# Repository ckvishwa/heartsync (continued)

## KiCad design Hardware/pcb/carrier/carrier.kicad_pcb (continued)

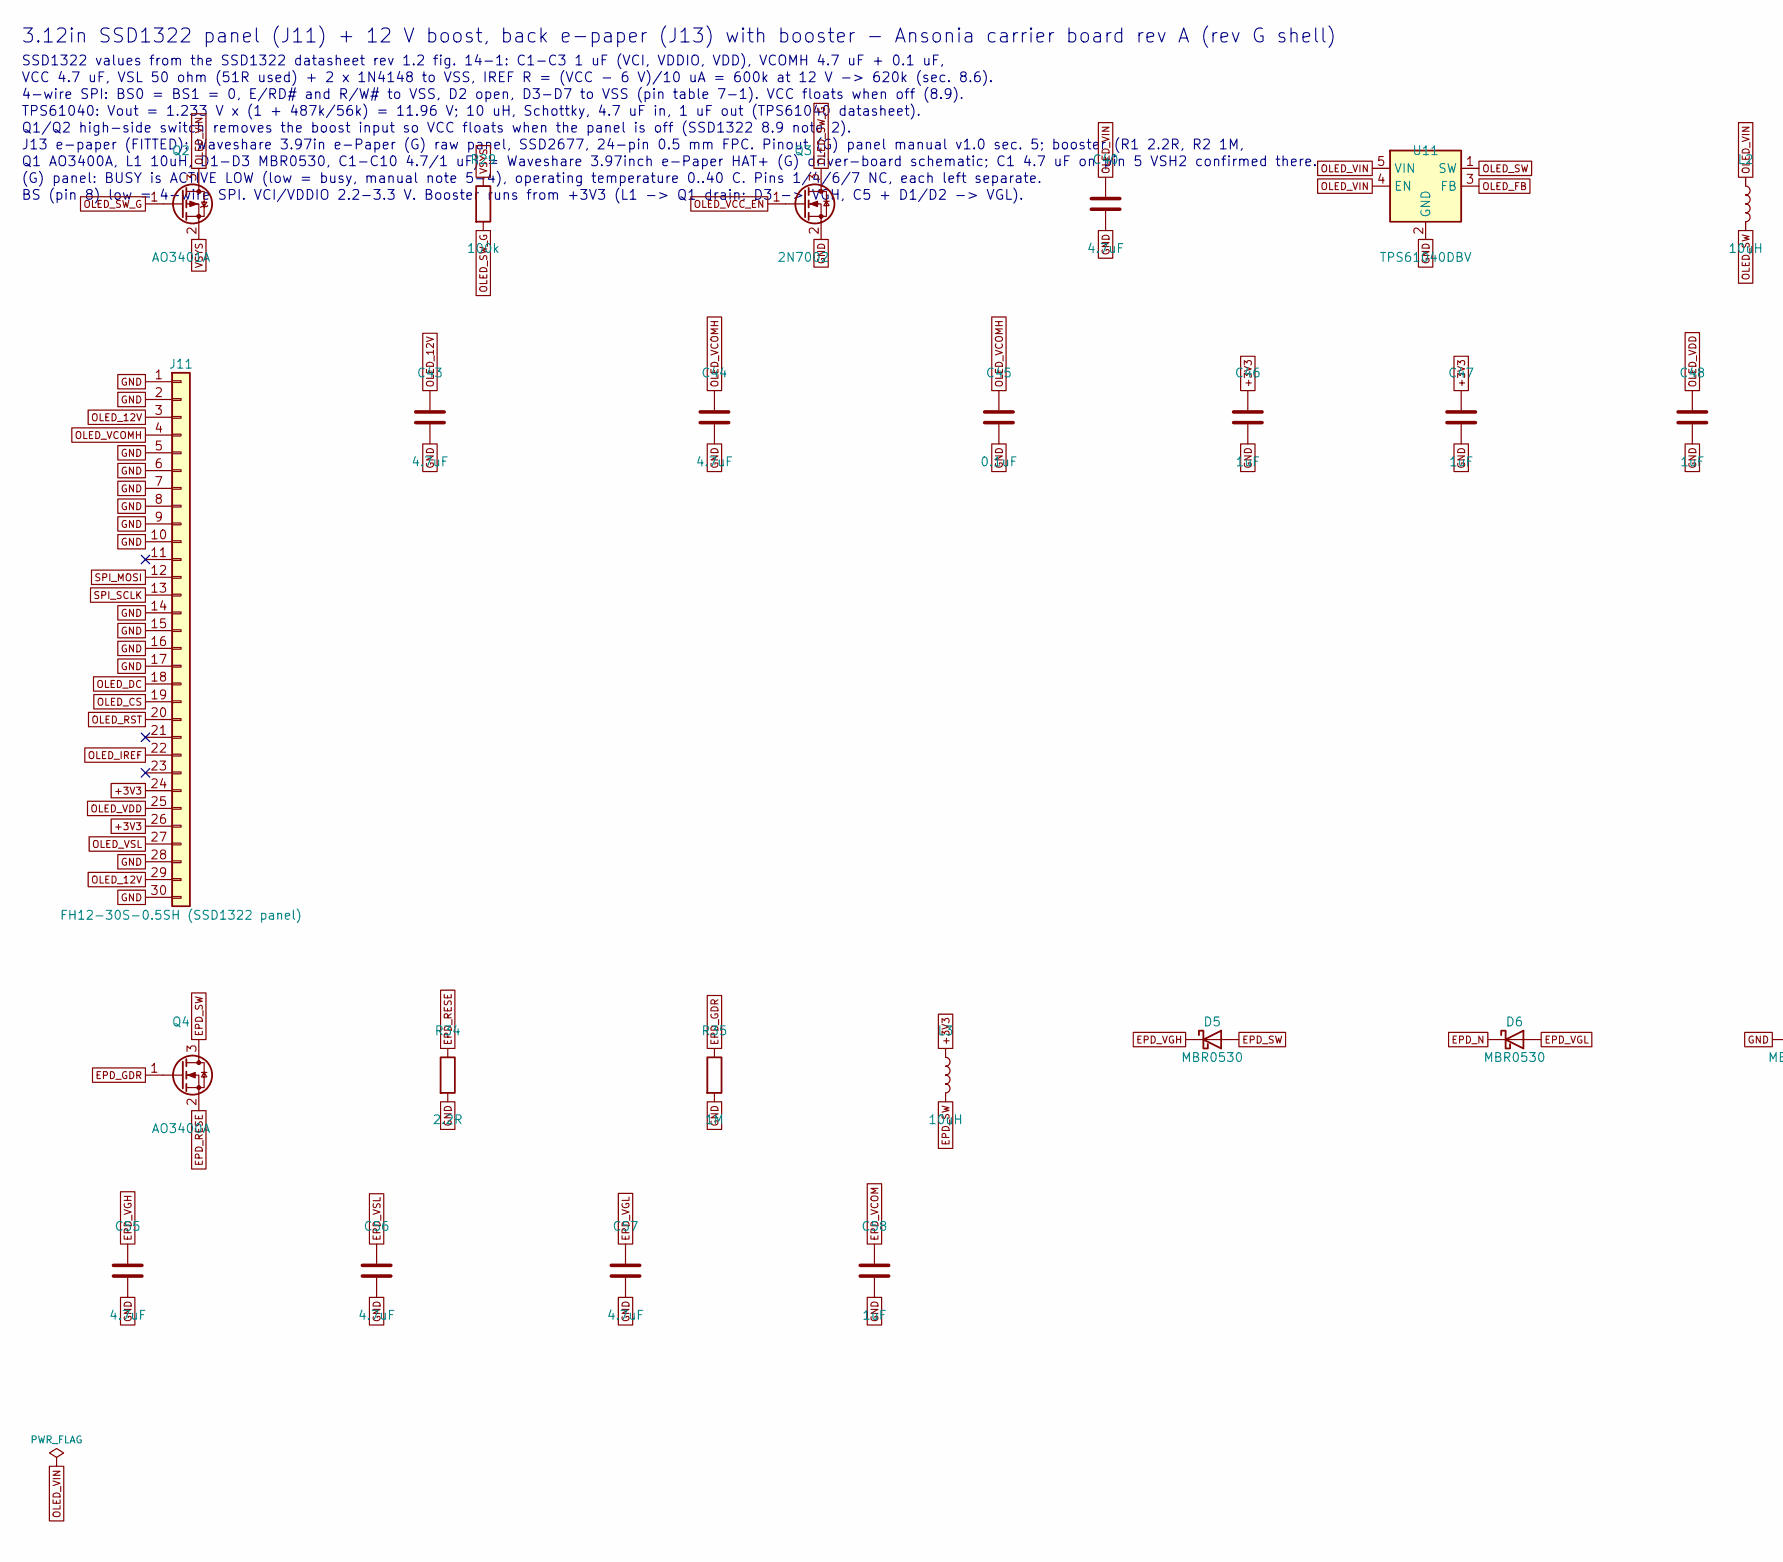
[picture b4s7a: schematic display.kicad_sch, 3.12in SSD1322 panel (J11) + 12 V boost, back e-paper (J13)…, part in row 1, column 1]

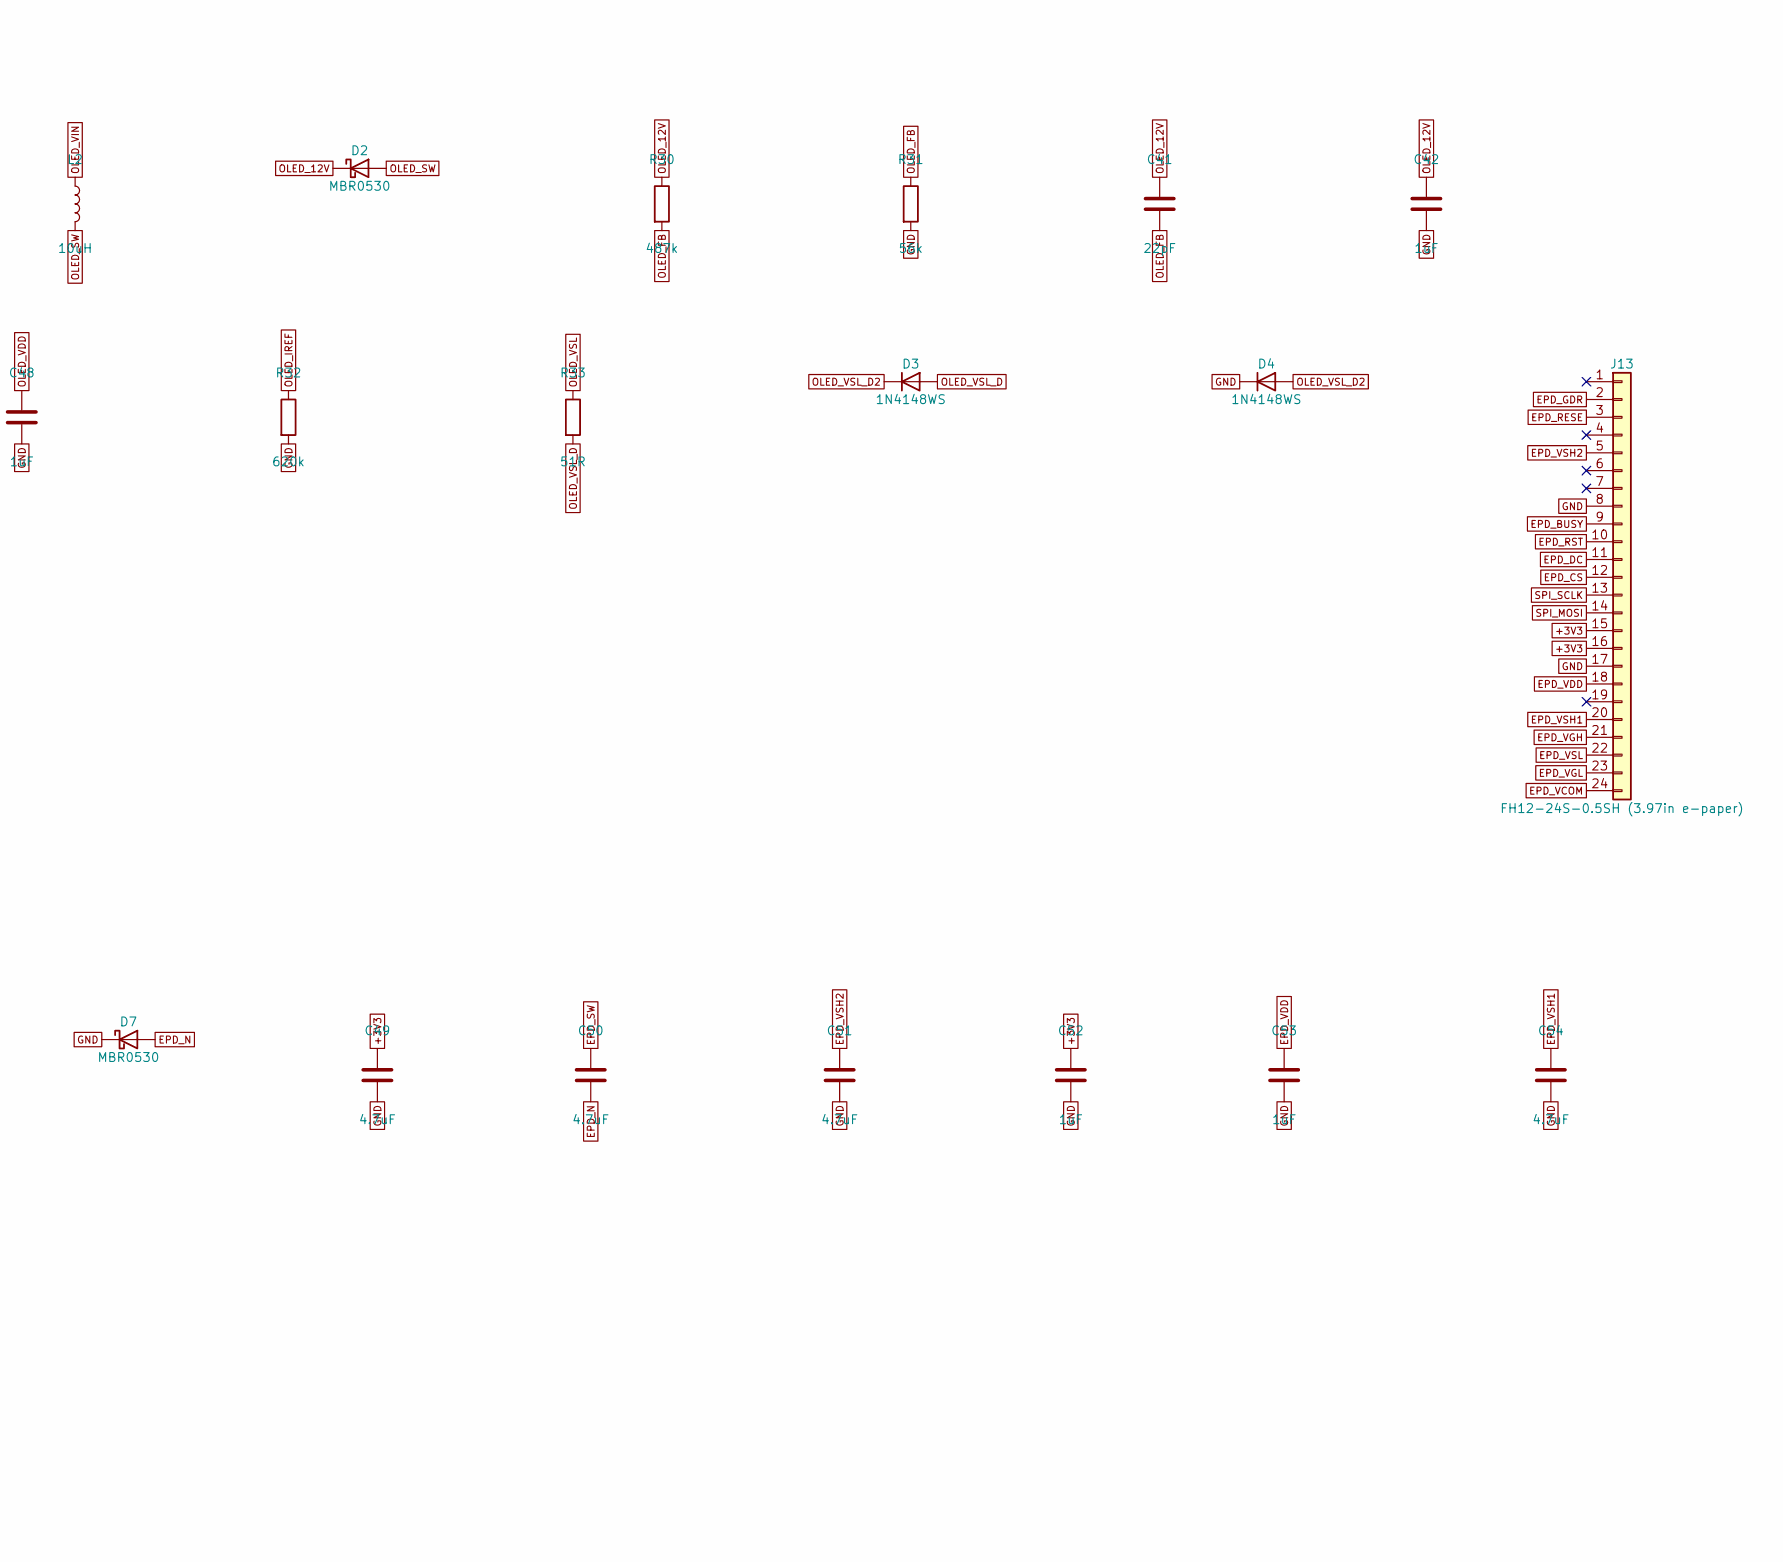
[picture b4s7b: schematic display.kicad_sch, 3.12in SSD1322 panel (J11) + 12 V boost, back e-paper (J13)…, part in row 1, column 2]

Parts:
C40: 4.7uF; C_0603_1608Metric
C41: 22pF; C_0402_1005Metric
C42, C52, C53, C58: 1uF; C_0603_1608Metric
C43, C44, C49, C50, C51, C54, C55, C56, C57: 4.7uF; C_0805_2012Metric
C45: 0.1uF; C_0402_1005Metric
C46, C47, C48: 1uF; C_0402_1005Metric
D2, D5, D6, D7: MBR0530; D_SOD-123
D3, D4: 1N4148WS; D_SOD-323
J11: FH12-30S-0.5SH (SSD1322 panel); Hirose_FH12-30S-0.5SH_1x30-1MP_P0.50mm_Horizontal; MPN FH12-30S-0.5SH(55)
J13: FH12-24S-0.5SH (3.97in e-paper); Hirose_FH12-24S-0.5SH_1x24-1MP_P0.50mm_Horizontal; MPN FH12-24S-0.5SH(55)
L2, L3: 10uH; L_1008_2520Metric; MPN DFE252012F-100M
Q2: AO3401A; SOT-23
Q3: 2N7002; SOT-23
Q4: AO3400A; SOT-23; MPN AO3400A
R29: 100k; R_0402_1005Metric
R30: 487k; R_0402_1005Metric
R31: 56k; R_0402_1005Metric
R32: 620k; R_0402_1005Metric
R33: 51R; R_0603_1608Metric
R34: 2.2R; R_0603_1608Metric
R35: 1M; R_0603_1608Metric
U11: TPS61040DBV; SOT-23-5; MPN TPS61040DBVR; LCSC C7722

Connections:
+3V3: C46.1, C47.1, C49.1, C52.1, J11.24, J11.26, J13.15, J13.16, L3.1; also elsewhere on the board
EPD_BUSY: J13.9; also elsewhere on the board
EPD_CS: J13.12; also elsewhere on the board
EPD_DC: J13.11; also elsewhere on the board
EPD_GDR: J13.2, Q4.1 (G), R35.1
EPD_N: C50.2, D6.1 (K), D7.2 (A)
EPD_RESE: J13.3, Q4.2 (S), R34.1
EPD_RST: J13.10; also elsewhere on the board
EPD_SW: C50.1, D5.2 (A), L3.2, Q4.3 (D)
EPD_VCOM: C58.1, J13.24
EPD_VDD: C53.1, J13.18
EPD_VGH: C55.1, D5.1 (K), J13.21
EPD_VGL: C57.1, D6.2 (A), J13.23
EPD_VSH1: C54.1, J13.20
EPD_VSH2: C51.1, J13.5
EPD_VSL: C56.1, J13.22
GND: C40.2, C42.2, C43.2, C44.2, C45.2, C46.2, C47.2, C48.2, C49.2, C51.2, C52.2, C53.2, C54.2, C55.2, C56.2, C57.2, C58.2, D4.1 (K), D7.1 (K), J11.1, J11.2, J11.5, J11.6, J11.7, J11.8, J11.9, J11.10, J11.14, J11.15, J11.16, J11.17, J11.28, J11.30, J13.8, J13.17, Q3.2 (S), R31.2, R32.2, R34.2, R35.2, U11.2 (GND); also elsewhere on the board
OLED_12V: C41.1, C42.1, C43.1, D2.1 (K), J11.3, J11.29, R30.1
OLED_CS: J11.19; also elsewhere on the board
OLED_DC: J11.18; also elsewhere on the board
OLED_FB: C41.2, R30.2, R31.1, U11.3 (FB)
OLED_IREF: J11.22, R32.1
OLED_RST: J11.20; also elsewhere on the board
OLED_SW: D2.2 (A), L2.2, U11.1 (SW)
OLED_SW_G: Q2.1 (G), Q3.3 (D), R29.2
OLED_VCC_EN: Q3.1 (G); also elsewhere on the board
OLED_VCOMH: C44.1, C45.1, J11.4
OLED_VDD: C48.1, J11.25
OLED_VIN: C40.1, L2.1, Q2.3 (D), U11.4 (EN), U11.5 (VIN)
OLED_VSL: J11.27, R33.1
OLED_VSL_D: D3.2 (A), R33.2
OLED_VSL_D2: D3.1 (K), D4.2 (A)
SPI_MOSI: J11.12, J13.14; also elsewhere on the board
SPI_SCLK: J11.13, J13.13; also elsewhere on the board
VSYS: Q2.2 (S), R29.1; also elsewhere on the board

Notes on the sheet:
3.12in SSD1322 panel (J11) + 12 V boost, back e-paper (J13) with booster - Ansonia carrier board rev A (rev G shell)
SSD1322 values from the SSD1322 datasheet rev 1.2 fig. 14-1: C1-C3 1 uF (VCI, VDDIO, VDD), VCOMH 4.7 uF + 0.1 uF,
VCC 4.7 uF, VSL 50 ohm (51R used) + 2 x 1N4148 to VSS, IREF R = (VCC - 6 V)/10 uA = 600k at 12 V -> 620k (sec. 8.6).
4-wire SPI: BS0 = BS1 = 0, E/RD# and R/W# to VSS, D2 open, D3-D7 to VSS (pin table 7-1). VCC floats when off (8.9).
TPS61040: Vout = 1.233 V x (1 + 487k/56k) = 11.96 V; 10 uH, Schottky, 4.7 uF in, 1 uF out (TPS61040 datasheet).
Q1/Q2 high-side switch removes the boost input so VCC floats when the panel is off (SSD1322 8.9 note 2).
J13 e-paper (FITTED): Waveshare 3.97in e-Paper (G) raw panel, SSD2677, 24-pin 0.5 mm FPC. Pinout (G) panel manual v1.0 sec. 5; booster (R1 2.2R, R2 1M,
Q1 AO3400A, L1 10uH, D1-D3 MBR0530, C1-C10 4.7/1 uF) = Waveshare 3.97inch e-Paper HAT+ (G) driver-board schematic; C1 4.7 uF on pin 5 VSH2 confirmed there.
(G) panel: BUSY is ACTIVE LOW (low = busy, manual note 5-4), operating temperature 0..40 C. Pins 1/4/6/7 NC, each left separate.
BS (pin 8) low = 4-wire SPI. VCI/VDDIO 2.2-3.3 V. Booster runs from +3V3 (L1 -> Q1 drain; D3 -> VGH, C5 + D1/D2 -> VGL).

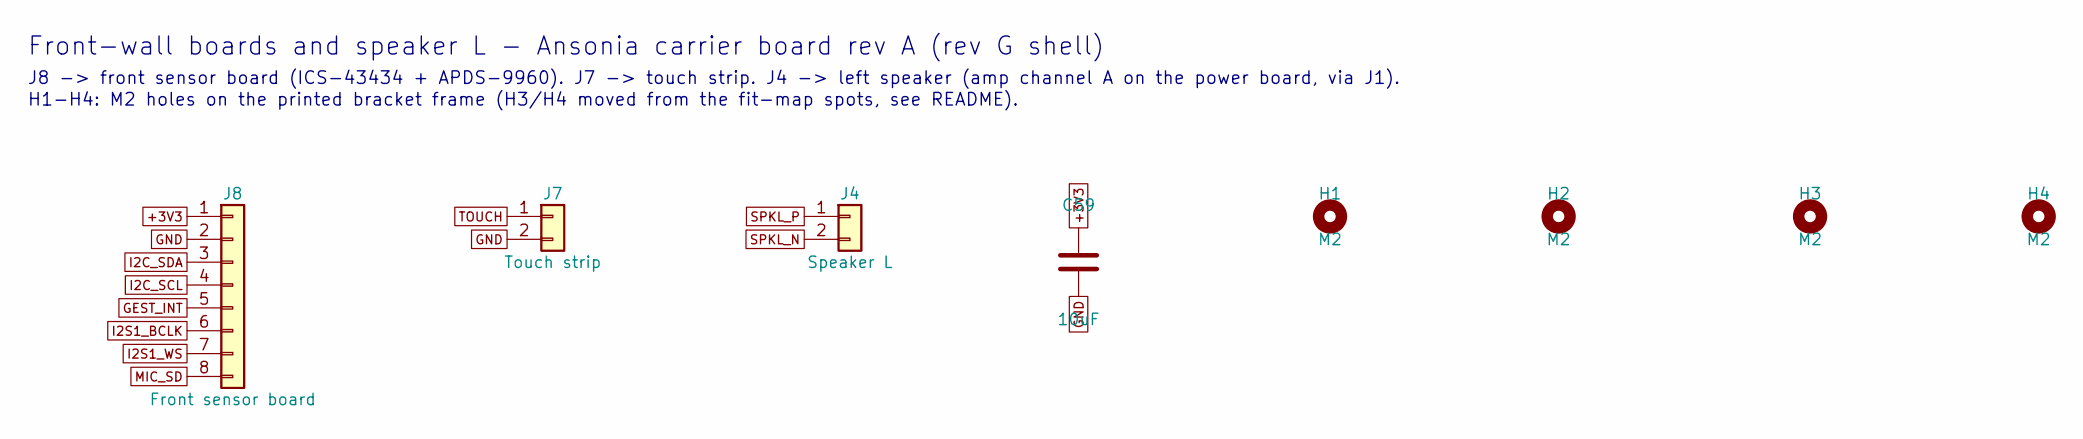
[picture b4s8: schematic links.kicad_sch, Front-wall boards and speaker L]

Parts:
C59: 10uF; C_0603_1608Metric
H1, H2, H3, H4: M2; MountingHole_2.2mm_M2
J4: Speaker L; JST_SH_SM02B-SRSS-TB_1x02-1MP_P1.00mm_Horizontal
J7: Touch strip; JST_SH_SM02B-SRSS-TB_1x02-1MP_P1.00mm_Horizontal
J8: Front sensor board; JST_SH_SM08B-SRSS-TB_1x08-1MP_P1.00mm_Horizontal

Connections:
+3V3: C59.1, J8.1; also elsewhere on the board
GEST_INT: J8.5; also elsewhere on the board
GND: C59.2, J7.2, J8.2; also elsewhere on the board
I2C_SCL: J8.4; also elsewhere on the board
I2C_SDA: J8.3; also elsewhere on the board
I2S1_BCLK: J8.6; also elsewhere on the board
I2S1_WS: J8.7; also elsewhere on the board
MIC_SD: J8.8; also elsewhere on the board
SPKL_N: J4.2; also elsewhere on the board
SPKL_P: J4.1; also elsewhere on the board
TOUCH: J7.1; also elsewhere on the board

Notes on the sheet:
Front-wall boards and speaker L - Ansonia carrier board rev A (rev G shell)
J8 -> front sensor board (ICS-43434 + APDS-9960). J7 -> touch strip. J4 -> left speaker (amp channel A on the power board, via J1).
H1-H4: M2 holes on the printed bracket frame (H3/H4 moved from the fit-map spots, see README).

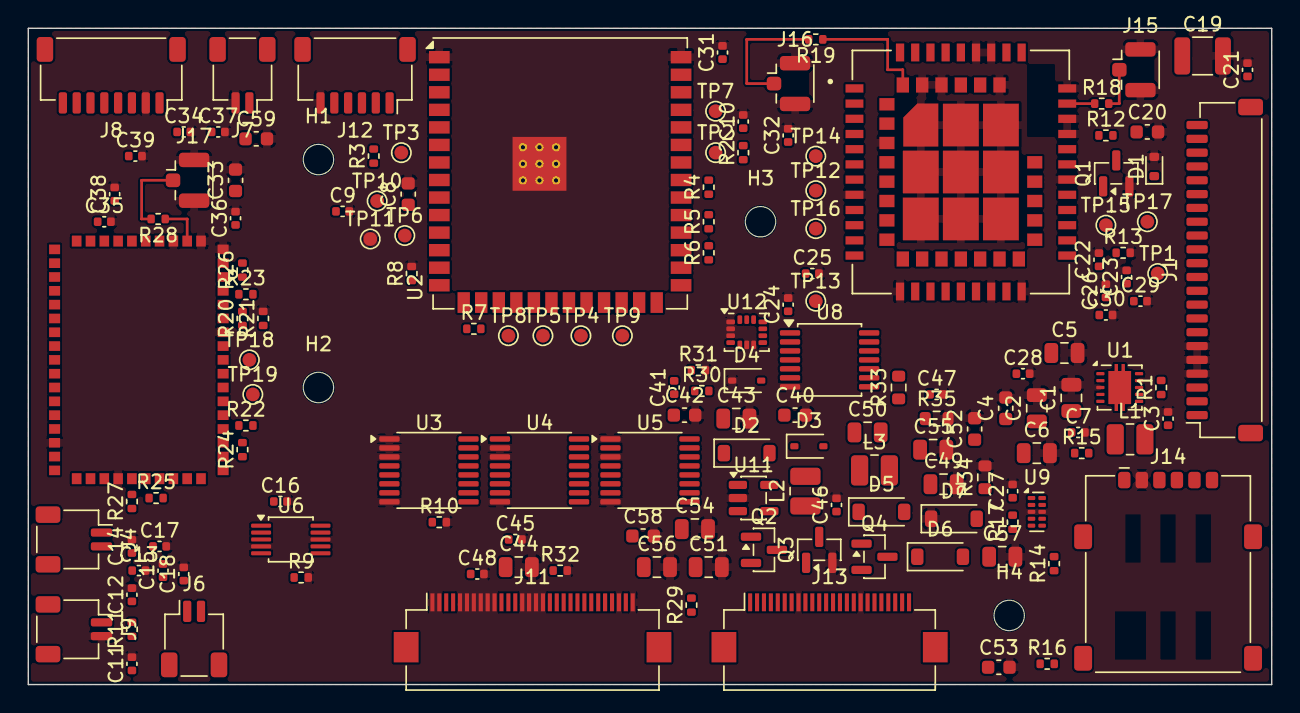
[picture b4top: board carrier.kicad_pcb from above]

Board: 4 copper layers, 90.0 x 47.5 mm, 156 parts (0 on the bottom side), 124 nets.

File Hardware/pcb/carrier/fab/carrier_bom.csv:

Comment,Designator,Footprint,LCSC Part #,MPN,Qty
22uF,"C1,C2,C5,C6",C_0805_2012Metric,,,4
1uF,"C10,C16,C17,C24,C35,C46,C47,C48",C_0402_1005Metric,,,8
100uF,C19,C_1210_3225Metric,,,1
33pF,C22,C_0402_1005Metric,,,1
10pF,C23,C_0402_1005Metric,,,1
0.1uF,"C11,C12,C13,C14,C15,C18,C21,C25,C26,C27,C3,C34,C36,C37,C45,C7,C9",C_0402_1005Metric,,,17
10uF,"C20,C33,C4,C59,C8",C_0603_1608Metric,,,5
4.7uF,C40,C_0603_1608Metric,,,1
22pF,C41,C_0402_1005Metric,,,1
1uF,"C42,C52,C53,C58",C_0603_1608Metric,,,4
4.7uF,"C43,C44,C49,C50,C51,C54,C55,C56,C57",C_0805_2012Metric,,,9
ESD5Z5.0 (5 V TVS),D1,D_SOD-523,,,1
MBR0530,"D2,D5,D6,D7",D_SOD-123,,,4
1N4148WS,"D3,D4",D_SOD-323,,,2
Link to power board (SM22B-SRSS-TB),J1,JST_SH_SM22B-SRSS-TB_1x22-1MP_P1.00mm_Horizontal,,,1
FH12-30S-0.5SH (SSD1322 panel),J11,Hirose_FH12-30S-0.5SH_1x30-1MP_P0.50mm_Horizontal,,FH12-30S-0.5SH(55),1
Buttons (MUTE PWR VOL- VOL+ PLAY GND),J12,JST_SH_SM06B-SRSS-TB_1x06-1MP_P1.00mm_Horizontal,,,1
FH12-24S-0.5SH (3.97in e-paper),J13,Hirose_FH12-24S-0.5SH_1x24-1MP_P0.50mm_Horizontal,,FH12-24S-0.5SH(55),1
nano-SIM push-pull,J14,nanoSIM_GCT_SIM8060-6-0-14-00,,SIM8060-6-0-14-00-A,1
U.FL LTE,J15,U.FL_Hirose_U.FL-R-SMT-1_Vertical,,U.FL-R-SMT-1(10),1
U.FL GNSS,J16,U.FL_Hirose_U.FL-R-SMT-1_Vertical,,U.FL-R-SMT-1(10),1
U.FL BT,J17,U.FL_Hirose_U.FL-R-SMT-1_Vertical,,U.FL-R-SMT-1(10),1
Speaker L,J4,JST_SH_SM02B-SRSS-TB_1x02-1MP_P1.00mm_Horizontal,,,1
Haptic LRA,J6,JST_SH_SM02B-SRSS-TB_1x02-1MP_P1.00mm_Horizontal,,,1
Touch strip,J7,JST_SH_SM02B-SRSS-TB_1x02-1MP_P1.00mm_Horizontal,,,1
Front sensor board,J8,JST_SH_SM08B-SRSS-TB_1x08-1MP_P1.00mm_Horizontal,,,1
Mute LED,J9,JST_SH_SM02B-SRSS-TB_1x02-1MP_P1.00mm_Horizontal,,,1
2.2uH,L1,L_1008_2520Metric,,DFE252012F-2R2M=P2,1
10uH,"L2,L3",L_1008_2520Metric,,DFE252012F-100M,2
MMBT3904,Q1,SOT-23,,,1
AO3401A,Q2,SOT-23,,,1
2N7002,Q3,SOT-23,,,1
AO3400A,Q4,SOT-23,,AO3400A,1
100R,R1,R_0402_1005Metric,,,1
330R,R11,R_0402_1005Metric,,,1
22R,"R14,R15,R16",R_0402_1005Metric,,,3
0R,"R18,R19,R28",R_0402_1005Metric,,,3
10k,"R10,R13,R2,R21,R3,R6,R7,R9",R_0402_1005Metric,,,8
1k,"R20,R22,R23,R24,R25,R26,R27",R_0402_1005Metric,,,7
487k,R30,R_0402_1005Metric,,,1
56k,R31,R_0402_1005Metric,,,1
620k,R32,R_0402_1005Metric,,,1
51R,R33,R_0603_1608Metric,,,1
2.2R,R34,R_0603_1608Metric,,,1
1M,R35,R_0603_1608Metric,,,1
4.7k,"R12,R4,R5",R_0402_1005Metric,,,3
100k,"R29,R8",R_0402_1005Metric,,,2
TPS63001DRC,U1,Texas_DRC0010J,C28855,TPS63001DRCR,1
EWM104-BT5125(I2S),U10,EWM104-BT5125,,EWM104-BT5125(I2S),1
TPS61040DBV,U11,SOT-23-5,C7722,TPS61040DBVR,1
LSM6DSOX,U12,LGA-14_3x2.5mm_P0.5mm_LayoutBorder3x4y,,LSM6DSOXTR,1
ESP32-S3-WROOM-1U-N16R8,U2,ESP32-S3-WROOM-1U_NoVias,C3013946,ESP32-S3-WROOM-1U-N16R8,1
TCA9554PW (0x20),U3,TSSOP-16_4.4x5mm_P0.65mm,C86803,TCA9554PWR,1
TCA9554PW (0x21),U4,TSSOP-16_4.4x5mm_P0.65mm,C86803,TCA9554PWR,1
TCA9554PW (0x22),U5,TSSOP-16_4.4x5mm_P0.65mm,C86803,TCA9554PWR,1
DRV2605LDGS,U6,TSSOP-10_3x3mm_P0.5mm,C527464,DRV2605LDGSR,1
SIM7080G,U7,SIM7080G,C2687012,SIM7080G,1
TXB0104PW,U8,TSSOP-14_4.4x5mm_P0.65mm,C53406,TXB0104PWR,1
TPD4E05U06DQA,U9,USON-10_2.5x1.0mm_P0.5mm,,TPD4E05U06DQAR,1

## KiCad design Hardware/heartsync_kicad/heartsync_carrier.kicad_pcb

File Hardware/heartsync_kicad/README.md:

# heartsync carrier board v0.1 (KiCad)

Put this folder at `D:\SyncD\hardware\kicad\`.

| File | What it is |
|---|---|
| `heartsync_carrier.py` | The whole circuit as Python (SKiDL). Edit this, not the netlist. |
| `heartsync_carrier.net` | Generated netlist: 67 parts, 52 nets. Import into KiCad. |
| `heartsync_carrier_bom.csv` | Parts list with part numbers and notes |
| `place_board.py` | Run inside the KiCad PCB editor: outline, holes, placement, GND pours |

## Steps

1. `pip install skidl` (only needed to regenerate after edits), then `python heartsync_carrier.py`.
2. KiCad: new project `heartsync_carrier`, open the PCB editor.
3. File > Import > Netlist > `heartsync_carrier.net` > Update PCB. All footprints come from the
   standard KiCad library, so none should be missing.
4. Tools > Scripting Console:
   `exec(open(r"D:\SyncD\hardware\kicad\place_board.py").read())`
   It prints ok / FAIL per step.
5. Board Setup: set your fab's rules (JLCPCB 2-layer: 0.127 mm track/space, 0.3 mm drill).
6. Route. Power first (+5V to the amps and buck, 0.5 mm+), then I2S, USB pair, the rest.
   The Freerouting plugin can do a first pass; check it by eye after.
7. Inspect > Design Rules Checker until clean. File > Export > STEP, then check fit in Fusion.

There is no schematic sheet: the Python file is the schematic. To change the circuit, edit
the Python, run it again, and use Import Netlist again (KiCad keeps your placement and tracks
for parts that did not change).

## What is on the board

- ESP32-S3-WROOM-1U-N16R8 (ADR 0011): U.FL socket facing the top edge, 3 mm clear around it,
  external 2.4 GHz flex antenna on the shell wall. No antenna keepout.
- TLV62569 buck: 5 V to 3.3 V, 2 A
- 2x MAX98357A (left / right from one GPIO through R5, R6/R7), powered from 5 V
- DRV2605L haptic driver (LRA), BMI270 IMU (I2C 0x68), MAX17048 fuel gauge (on VBAT)
- USBLC6-2SC6 ESD on USB D+/D-
- TXS0102 level shifter (1.8 V SIM7080G to 3.3 V ESP32) and a BSS138 for SIM PWRKEY
- RESET and BOOT buttons, 7 test points (5V, 3V3, GND, VBAT, UART0 TX/RX, 1V8)
- 12 JST-SH connectors, all on the board edges

## Connectors

| Ref | Pins | To |
|---|---|---|
| J1 | 5V, 5V, GND, GND, D+, D-, ALERT | Power bank / USB-C module |
| J2 | VBAT, GND | Battery (fuel gauge and SIM supply) |
| J3 | VBAT, GND, TXD, RXD, PWRKEY, VDD_EXT | SIM7080G module (1.8 V I/O) |
| J4, J5 | +, - | Left / right speaker (J4 on the left edge, J5 on the right edge) |
| J6 | +, - | Haptic LRA |
| J7 | T1, T2, T3, GND | Touch strip |
| J8 | MIC_3V3, GND, SCK, WS, SD | INMP441 mic (power cut by mute switch) |
| J9 | 3V3 out, MIC_3V3 back | Mic mute: self-latching push button (7 x 7 mm, top edge) |
| J10 | 3V3, GND, SDA, SCL | VEML7700 light sensor |
| J11 | 3V3, GND, SCK, MOSI, CS, DC, RST | OLED (SPI) |
| J12 | 3V3, GND, LADDER, POWER | Button strip |

Button strip ladder (on the strip, each button to GND through its resistor, 10k pull-up on
this board): Vol- 0 ohm (0 V), Vol+ 3.3k (about 0.8 V), Play 10k (about 1.65 V).

## Check before ordering

- Every chip's pinout against its datasheet (taken from the official KiCad 10 symbols; the
  MAX17048 from its datasheet; the BMI270 from a community symbol).
- J1 ALERT: the power bank module's interrupt must be open-drain and at most 3.3 V.
- J3: if your SIM7080G board already has 3.3 V level shifting, bridge the TXS0102 or skip it.
- J11: the 2.7in OLED controller and connector are not chosen yet; J11 is a cable header for now.
- JST-SH orientation: rotate each connector so its cable entry faces the board edge.
- MAX98357A SD_MODE levels with R5-R7 (left > 1.4 V, right 0.77-1.4 V).

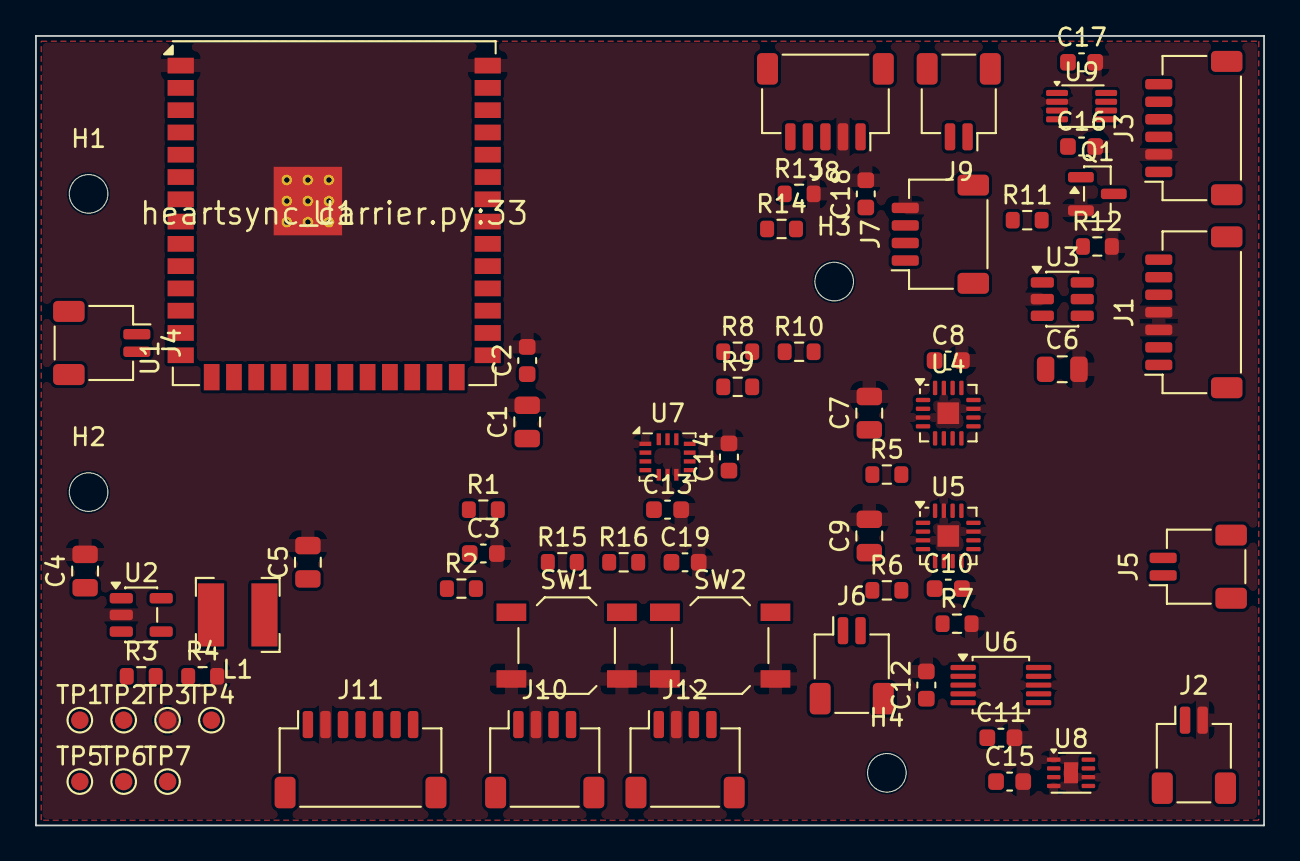
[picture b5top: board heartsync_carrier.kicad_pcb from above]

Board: 2 copper layers, 70.0 x 45.0 mm, 71 parts (0 on the bottom side), 52 nets, no tracks yet.

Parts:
C1, C4, C7, C9: 10uF; C_0805_2012Metric
C2, C8, C10, C13, C14, C15, C16, C17, C18, C19: 100nF; C_0603_1608Metric
C3, C11, C12: 1uF; C_0603_1608Metric
C5, C6: 22uF; C_0805_2012Metric
H1, H2, H3, H4: MountingHole_2.2mm_M2
J1: POWER: 5V,5V,GND,GND,D+,D-,ALERT (power bank / US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; JST_SH_SM07B-SRSS-TB_1x07-1MP_P1.00mm_Horizontal
J2: BATTERY SENSE: VBAT, GND (cell, for fuel gauge an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; JST_SH_SM02B-SRSS-TB_1x02-1MP_P1.00mm_Horizontal
J3: SIM7080G: VBAT,GND,TXD,RXD,PWRKEY,VDD_EXT; JST_SH_SM06B-SRSS-TB_1x06-1MP_P1.00mm_Horizontal
J4: SPEAKER LEFT; JST_SH_SM02B-SRSS-TB_1x02-1MP_P1.00mm_Horizontal
J5: SPEAKER RIGHT; JST_SH_SM02B-SRSS-TB_1x02-1MP_P1.00mm_Horizontal
J6: HAPTIC LRA; JST_SH_SM02B-SRSS-TB_1x02-1MP_P1.00mm_Horizontal
J7: TOUCH STRIP; JST_SH_SM04B-SRSS-TB_1x04-1MP_P1.00mm_Horizontal
J8: MIC INMP441: 3V3(muted),GND,SCK,WS,SD; JST_SH_SM05B-SRSS-TB_1x05-1MP_P1.00mm_Horizontal
J9: MUTE SWITCH: 3V3 out, mic rail back; JST_SH_SM02B-SRSS-TB_1x02-1MP_P1.00mm_Horizontal
J10: LIGHT SENSOR VEML7700; JST_SH_SM04B-SRSS-TB_1x04-1MP_P1.00mm_Horizontal
J11: OLED SPI; JST_SH_SM07B-SRSS-TB_1x07-1MP_P1.00mm_Horizontal
J12: BUTTON STRIP: 3V3,GND,LADDER,POWER; JST_SH_SM04B-SRSS-TB_1x04-1MP_P1.00mm_Horizontal
L1: 2.2uH; L_Bourns-SRN4018
Q1: BSS138; SOT-23
R1, R2, R5, R10, R15, R16: 10k; R_0603_1608Metric
R3: 453k 1%; R_0603_1608Metric
R4: 100k 1%; R_0603_1608Metric
R6: 68k; R_0603_1608Metric
R7: 47k; R_0603_1608Metric
R8, R9: 4.7k; R_0603_1608Metric
R11, R14: 1k; R_0603_1608Metric
R12, R13: 100k; R_0603_1608Metric
SW1: RESET; SW_SPST_TL3342
SW2: BOOT; SW_SPST_TL3342
TP1: +5V; TestPoint_Pad_D1.0mm
TP2: +3V3; TestPoint_Pad_D1.0mm
TP3: GND; TestPoint_Pad_D1.0mm
TP4: VBAT; TestPoint_Pad_D1.0mm
TP5: UART0 TX; TestPoint_Pad_D1.0mm
TP6: UART0 RX; TestPoint_Pad_D1.0mm
TP7: 1V8; TestPoint_Pad_D1.0mm
U1: ESP32-S3-WROOM-1U-N16R8; ESP32-S3-WROOM-1U_NoVias
U2: TLV62569DBV; SOT-23-5
U3: USBLC6-2SC6; SOT-23-6
U4, U5: MAX98357A; TQFN-16-1EP_3x3mm_P0.5mm_EP1.23x1.23mm
U6: DRV2605LDGS; TSSOP-10_3x3mm_P0.5mm
U7: BMI270; Bosch_LGA-14_3x2.5mm_P0.5mm
U8: MAX17048G+T10; TDFN-8-1EP_2x2mm_P0.5mm_EP0.8x1.2mm
U9: TXS0102DCU; VSSOP-8_2.3x2mm_P0.5mm

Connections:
+3V3: C1.1, C2.1, C5.1, C12.1, C13.1, C14.1, C17.1, J9.1, J10.1, J11.1, J12.1, L1.2, R1.1, R2.1, R3.1, R8.1, R9.1, R10.1, R15.1, R16.1, TP2.1, U1.2, U6.5, U6.6, U6.10, U7.5, U7.8, U7.12, U9.7
+5V: C4.1, C6.1, C7.1, C8.1, C9.1, C10.1, J1.1, J1.2, TP1.1, U2.1, U2.4, U3.5, U4.7, U4.8, U5.7, U5.8
ALERT_N: J1.7, R10.2, U1.23, U8.5
AMP_L_SDMODE: R5.2, U4.4
AMP_R_SDMODE: R6.2, R7.1, U5.4
AMP_SD: R5.1, R6.1, U1.11
BTN_ADC: J12.3, R15.2, U1.5
BTN_PWR_N: C19.1, J12.4, R16.2, U1.6
DRV_REG: C11.1, U6.1
ESP_BOOT: R2.2, SW2.1, U1.27
ESP_EN: C3.1, R1.2, SW1.1, U1.3
ESP_RX: U1.35, U9.8
ESP_TX: U1.34, U9.1
GND: C1.2, C2.2, C3.2, C4.2, C5.2, C6.2, C7.2, C8.2, C9.2, C10.2, C11.2, C12.2, C13.2, C14.2, C15.2, C16.2, C17.2, C18.2, C19.2, J1.3, J1.4, J2.2, J3.2, J7.4, J8.2, J10.2, J11.2, J12.2, Q1.2, R4.2, R7.2, R12.2, R13.2, SW1.2, SW2.2, TP3.1, U1.1, U1.40, U1.41, U2.2, U3.2, U4.3, U4.11, U4.15, U4.17, U5.3, U5.11, U5.15, U5.17, U6.4, U6.8, U7.1, U7.6, U7.7, U8.1, U8.4, U8.6, U8.9, U9.2
I2C_SCL: J10.4, R9.2, U1.17, U6.2, U7.13, U8.7
I2C_SDA: J10.3, R8.2, U1.12, U6.3, U7.14, U8.8
I2S_BCLK: U1.8, U4.16, U5.16
I2S_DIN: U1.10, U4.1, U5.1
I2S_LRCLK: U1.9, U4.14, U5.14
IMU_INT: U1.7, U7.4
LRA+: J6.1, U6.7
LRA-: J6.2, U6.9
MIC_3V3: C18.1, J8.1, J9.2, R13.1, R14.1
MIC_SCK: J8.3, U1.31
MIC_SD: J8.5, U1.33
MIC_WS: J8.4, U1.32
MUTE_SENSE: R14.2, U1.25
OLED_CS: J11.5, U1.18
OLED_DC: J11.6, U1.21
OLED_MOSI: J11.4, U1.19
OLED_RST: J11.7, U1.22
OLED_SCK: J11.3, U1.20
Q1_GATE: Q1.1, R11.2, R12.1
REG_FB: R3.2, R4.1, U2.5
REG_SW: L1.1, U2.3
SIM_PWRKEY: J3.5, Q1.3
SIM_PWRKEY_CTL: R11.1, U1.24
SIM_RXD_1V8: J3.4, U9.4
SIM_TXD_1V8: J3.3, U9.5
SPK_L+: J4.1, U4.9
SPK_L-: J4.2, U4.10
SPK_R+: J5.1, U5.9
SPK_R-: J5.2, U5.10
TOUCH1: J7.1, U1.39
TOUCH2: J7.2, U1.38
TOUCH3: J7.3, U1.4
UART0_RX: TP6.1, U1.36
UART0_TX: TP5.1, U1.37
USB_D+: J1.5, U1.14, U3.3, U3.4
USB_D-: J1.6, U1.13, U3.1, U3.6
VBAT: C15.1, J2.1, J3.1, TP4.1, U8.2, U8.3
VDD_EXT_1V8: C16.1, J3.6, TP7.1, U9.3, U9.6

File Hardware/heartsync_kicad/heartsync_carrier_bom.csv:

ref,value,footprint,mpn,note
U1,ESP32-S3-WROOM-1U-N16R8,heartsync:ESP32-S3-WROOM-1U_NoVias,ESP32-S3-WROOM-1U-N16R8,"U.FL socket faces the board top edge, 3 mm clear"
C1,10uF,Capacitor_SMD:C_0805_2012Metric,,"ESP32 bulk, next to pin 2"
C2,100nF,Capacitor_SMD:C_0603_1608Metric,,ESP32 decoupling
R1,10k,Resistor_SMD:R_0603_1608Metric,,EN pull-up
C3,1uF,Capacitor_SMD:C_0603_1608Metric,,EN delay
R2,10k,Resistor_SMD:R_0603_1608Metric,,IO0 pull-up
SW1,RESET,Button_Switch_SMD:SW_SPST_TL3342,TL3342,
SW2,BOOT,Button_Switch_SMD:SW_SPST_TL3342,TL3342,
U2,TLV62569DBV,Package_TO_SOT_SMD:SOT-23-5,TLV62569DBVR,"2 A buck, 5 V -> 3.3 V"
L1,2.2uH,Inductor_SMD:L_Bourns-SRN4018,SRN4018-2R2M,"2.2 uH, >= 2 A"
R3,453k 1%,Resistor_SMD:R_0603_1608Metric,,FB top: Vout = 0.6 V x (1 + 453k/100k) = 3.32 V
R4,100k 1%,Resistor_SMD:R_0603_1608Metric,,FB bottom
C4,10uF,Capacitor_SMD:C_0805_2012Metric,,Buck input
C5,22uF,Capacitor_SMD:C_0805_2012Metric,,Buck output
C6,22uF,Capacitor_SMD:C_0805_2012Metric,,5 V bulk at the power connector
U3,USBLC6-2SC6,Package_TO_SOT_SMD:SOT-23-6,USBLC6-2SC6,
U4,MAX98357A,Package_DFN_QFN:TQFN-16-1EP_3x3mm_P0.5mm_EP1.23x1.23mm,MAX98357AETE+,Left amp
C7,10uF,Capacitor_SMD:C_0805_2012Metric,,U4 bulk
C8,100nF,Capacitor_SMD:C_0603_1608Metric,,U4 decoupling
U5,MAX98357A,Package_DFN_QFN:TQFN-16-1EP_3x3mm_P0.5mm_EP1.23x1.23mm,MAX98357AETE+,Right amp
C9,10uF,Capacitor_SMD:C_0805_2012Metric,,U5 bulk
C10,100nF,Capacitor_SMD:C_0603_1608Metric,,U5 decoupling
R5,10k,Resistor_SMD:R_0603_1608Metric,,U4 SD_MODE: about 3.0 V = left
R6,68k,Resistor_SMD:R_0603_1608Metric,,U5 SD_MODE divider top
R7,47k,Resistor_SMD:R_0603_1608Metric,,U5 SD_MODE divider bottom: about 1.0-1.1 V = right
U6,DRV2605LDGS,Package_SO:TSSOP-10_3x3mm_P0.5mm,DRV2605LDGSR,"LRA mode, EN tied high"
C11,1uF,Capacitor_SMD:C_0603_1608Metric,,DRV2605L REG
C12,1uF,Capacitor_SMD:C_0603_1608Metric,,DRV2605L VDD
U7,BMI270,Package_LGA:Bosch_LGA-14_3x2.5mm_P0.5mm,BMI270,"CSB high = I2C, SDO low = 0x68"
C13,100nF,Capacitor_SMD:C_0603_1608Metric,,BMI270 VDD
C14,100nF,Capacitor_SMD:C_0603_1608Metric,,BMI270 VDDIO
U8,MAX17048G+T10,Package_DFN_QFN:TDFN-8-1EP_2x2mm_P0.5mm_EP0.8x1.2mm,MAX17048G+T10,Powered from and sensing the cell
C15,100nF,Capacitor_SMD:C_0603_1608Metric,,MAX17048 VDD
R8,4.7k,Resistor_SMD:R_0603_1608Metric,,I2C pull-up
R9,4.7k,Resistor_SMD:R_0603_1608Metric,,I2C pull-up
R10,10k,Resistor_SMD:R_0603_1608Metric,,Shared open-drain alert
U9,TXS0102DCU,Package_SO:VSSOP-8_2.3x2mm_P0.5mm,TXS0102DCUR,"A side 1.8 V (SIM), B side 3.3 V (ESP32)"
C16,100nF,Capacitor_SMD:C_0603_1608Metric,,TXS0102 VCCA
C17,100nF,Capacitor_SMD:C_0603_1608Metric,,TXS0102 VCCB
Q1,BSS138,Package_TO_SOT_SMD:SOT-23,BSS138,Pulls SIM PWRKEY low
R11,1k,Resistor_SMD:R_0603_1608Metric,,Gate series
R12,100k,Resistor_SMD:R_0603_1608Metric,,"Gate pull-down, PWRKEY idle at boot"
R13,100k,Resistor_SMD:R_0603_1608Metric,,Mic rail reads low when the mute switch is open
R14,1k,Resistor_SMD:R_0603_1608Metric,,Mute sense to IO48
C18,100nF,Capacitor_SMD:C_0603_1608Metric,,Mic rail
R15,10k,Resistor_SMD:R_0603_1608Metric,,Button ladder top (ladder resistors on the button strip)
R16,10k,Resistor_SMD:R_0603_1608Metric,,Power button pull-up
C19,100nF,Capacitor_SMD:C_0603_1608Metric,,Power button debounce
J1,"POWER: 5V,5V,GND,GND,D+,D-,ALERT (power bank / USB-C module)",Connector_JST:JST_SH_SM07B-SRSS-TB_1x07-1MP_P1.00mm_Horizontal,JST SM07B-SRSS-TB,"POWER: 5V,5V,GND,GND,D+,D-,ALERT (power bank / USB-C module)"
J2,"BATTERY SENSE: VBAT, GND (cell, for fuel gauge and SIM)",Connector_JST:JST_SH_SM02B-SRSS-TB_1x02-1MP_P1.00mm_Horizontal,JST SM02B-SRSS-TB,"BATTERY SENSE: VBAT, GND (cell, for fuel gauge and SIM)"
J3,"SIM7080G: VBAT,GND,TXD,RXD,PWRKEY,VDD_EXT",Connector_JST:JST_SH_SM06B-SRSS-TB_1x06-1MP_P1.00mm_Horizontal,JST SM06B-SRSS-TB,"SIM7080G: VBAT,GND,TXD,RXD,PWRKEY,VDD_EXT"
J4,SPEAKER LEFT,Connector_JST:JST_SH_SM02B-SRSS-TB_1x02-1MP_P1.00mm_Horizontal,JST SM02B-SRSS-TB,SPEAKER LEFT
J5,SPEAKER RIGHT,Connector_JST:JST_SH_SM02B-SRSS-TB_1x02-1MP_P1.00mm_Horizontal,JST SM02B-SRSS-TB,SPEAKER RIGHT
J6,HAPTIC LRA,Connector_JST:JST_SH_SM02B-SRSS-TB_1x02-1MP_P1.00mm_Horizontal,JST SM02B-SRSS-TB,HAPTIC LRA
J7,TOUCH STRIP,Connector_JST:JST_SH_SM04B-SRSS-TB_1x04-1MP_P1.00mm_Horizontal,JST SM04B-SRSS-TB,TOUCH STRIP
J8,"MIC INMP441: 3V3(muted),GND,SCK,WS,SD",Connector_JST:JST_SH_SM05B-SRSS-TB_1x05-1MP_P1.00mm_Horizontal,JST SM05B-SRSS-TB,"MIC INMP441: 3V3(muted),GND,SCK,WS,SD"
J9,"MUTE SWITCH: 3V3 out, mic rail back",Connector_JST:JST_SH_SM02B-SRSS-TB_1x02-1MP_P1.00mm_Horizontal,JST SM02B-SRSS-TB,"MUTE SWITCH: 3V3 out, mic rail back"
J10,LIGHT SENSOR VEML7700,Connector_JST:JST_SH_SM04B-SRSS-TB_1x04-1MP_P1.00mm_Horizontal,JST SM04B-SRSS-TB,LIGHT SENSOR VEML7700
J11,OLED SPI,Connector_JST:JST_SH_SM07B-SRSS-TB_1x07-1MP_P1.00mm_Horizontal,JST SM07B-SRSS-TB,OLED SPI
J12,"BUTTON STRIP: 3V3,GND,LADDER,POWER",Connector_JST:JST_SH_SM04B-SRSS-TB_1x04-1MP_P1.00mm_Horizontal,JST SM04B-SRSS-TB,"BUTTON STRIP: 3V3,GND,LADDER,POWER"
TP1,+5V,TestPoint:TestPoint_Pad_D1.0mm,,
TP2,+3V3,TestPoint:TestPoint_Pad_D1.0mm,,
TP3,GND,TestPoint:TestPoint_Pad_D1.0mm,,
TP4,VBAT,TestPoint:TestPoint_Pad_D1.0mm,,
TP5,UART0 TX,TestPoint:TestPoint_Pad_D1.0mm,,
TP6,UART0 RX,TestPoint:TestPoint_Pad_D1.0mm,,
TP7,1V8,TestPoint:TestPoint_Pad_D1.0mm,,

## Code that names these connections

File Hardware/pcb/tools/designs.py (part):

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
    # ---------------------------------------------------------------- power
    s = d.sheet("power", "Power in, 3V3 buck-boost")
    s.note("J1 pin 1-3 VSYS (= battery voltage 3.0-4.2 V behind the reverse-battery FET, not a regulated rail), 4-6 GND; JST SH contacts are 1 A each. Pin 21 QI_EN (expander 0x22 P6), 22 PWR_KEY.")
    s.note("U2 TPS63001 fixed 3.3 V buck-boost: L 2.2 uH, Cin 10 uF, VINA RC 100R/0.1 uF per TPS63001 datasheet fig. 1;")
    s.note("output 2 x 22 uF (Wi-Fi TX bursts).")
    conn(s, "J1", 22, J1_NETS, value="Link to power board (SM22B-SRSS-TB)")
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
    # ---------------------------------------------------------------- cellular
    s = d.sheet("cellular", "SIM7080G LTE-M/NB-IoT + GNSS, nano-SIM")
    s.note("VBAT straight from VSYS: 100 uF + 10 uF + 0.1 uF + 33 pF + 10 pF and a TVS at the pins (SIM7080G HD 3.1, fig. 5).")
    s.note("VBAT range 2.7-4.8 V (SIM7080G HD checklist). UART is 1.8 V (VDD_EXT): TXB0104 shifts to 3.3 V.")
    s.note("BOOT_CFG (20) and SPI_MOSI (49) must not be pulled up before power-up: BOOT_CFG goes to a test pad only.")
    s.note("RF: 50 ohm CPWG, pi-match pads (0R + 2 x DNP) at both U.FL. Test pads for USB (firmware update).")
    simpins = {"UART1_TXD": "SIM_TXD", "UART1_RXD": "SIM_RXD", "DTR": "SIM_DTR", "SIM_DATA": "SIM_DATA",
               "SIM_CLK": "SIM_CLK", "SIM_RST": "SIM_RST", "SIM_VDD": "SIM_VDD", "BOOT_CFG": "SIM_BOOT_CFG",
               "USB_VBUS": "SIM_USB_VBUS", "USB_DP": "SIM_USB_DP", "USB_DM": "SIM_USB_DM", "RF_ANT": "LTE_RF",
               "VBAT": VSYS, "PWRKEY": "SIM_PWRKEY", "VDD_EXT": "VDD_EXT", "STATUS": "SIM_STATUS",
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    s.C("0.1uF", V3, GND)
    s.part("Q", "Transistor_BJT:MMBT3904", "MMBT3904", "", {"B": "SIM_PWRKEY_B", "E": GND, "C": "SIM_PWRKEY"})
    s.R("4.7k", "SIM_PWRKEY_CTL", "SIM_PWRKEY_B")
    s.R("10k", "SIM_PWRKEY_B", GND, Note="holds PWRKEY released while the expander pin is an input (100k pull-up)")
    # SIM card
    s.part("J14", "Connector:SIM_Card", "nano-SIM push-pull", "Connector_Card:nanoSIM_GCT_SIM8060-6-0-14-00", {
        "VCC": "SIM_VDD", "RST": "SIMC_RST", "CLK": "SIMC_CLK", "GND": GND, "VPP": None, "I/O": "SIMC_DATA"},
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    s.note("Port 2 = VOUT2 (a USB-A style 5 V output, 2.2 uF) wired to Type-C J3 with Rp 22k from VBUS2 on CC1/CC2 (1.5 A). The datasheet lists")
    s.note("'1 Type-C in/out + 1 Type-C out (customize)' without a part number: ask Injoinic. Unused: VOUT1/DPA1/DMA1, VIN/DPB/DMB (Micro-B), CL (lightning), LED4/LED6.")
    s.note("IMPORTANT: VSYS on this IC is the internal DC-DC bus (5-12 V), NOT a system rail. The system (VSYS net) is the battery behind Q (0R link).")
    s.note("L1 2.2 uH between LX and BAT (fig. 25), BST 0.1 uF to LX, VCC 2.2 uF, NTC 100 nF at the pin, FCAP 22.1k = 10 Ah (R x 0.448 mAh).")
    s.note("Battery: J4 Amass MR30PW-M (BAT+ pin 1, BAT- pin 3), TP1/TP2 4x4 pads = DNP alternative for 18 AWG leads, J5 (JST SH 2) = pack NTC (10k).")
    s.note("Design current: 5 A continuous / 8 A peak from the cell (pack PCM limit unknown). F1 8 A, Q = reverse-battery PFET (DMP3013SFV), D = SMF5.0A TVS.")
    s.part("U1", "ansonia:IP5356M", "IP5356M_LBZ_CB", "", {
        "SDA": "I2C_SDA", "INT": "PWR_INT", "SCL": "I2C_SCL", "LX": "IP_LX", "BST": "IP_BST", "LED4": None,
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    s.C("0.1uF", "IP_VSYS", GND)
    s.C("22uF", "BAT_SW", GND, "0805")
    s.C("0.1uF", "BAT_SW", GND, Note="C1")
    s.C("0.1uF", "NTC", GND, Note="C13, close to the pin")
    s.R("22.1k", "IP_FCAP", GND, Note="battery capacity = R x 0.448 mAh = 9.9 Ah")
    s.C("2.2uF", "VBUS1", GND, "0603", Note="C5 at the VBUS pins")
    s.C("2.2uF", "VBUS1", GND, "0603")
    s.C("0.1uF", "VBUS1", GND)
    s.C("2.2uF", "VBUS2", GND, "0603", Note="VOUT2")
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
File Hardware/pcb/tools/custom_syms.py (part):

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def sim7080g():
    t = {1: ("UART1_TXD", O), 2: ("UART1_RXD", I), 3: ("RTS", I), 4: ("CTS", O), 5: ("DCD", O), 6: ("DTR", I),
         7: ("RI", O), 9: ("PCM_DIN", I), 10: ("PCM_DOUT", O), 11: ("PCM_CLK", B), 12: ("PCM_SYNC", B),
         14: ("GPIO5", B), 15: ("SIM_DATA", B), 16: ("SIM_CLK", O), 17: ("SIM_RST", O), 18: ("SIM_VDD", PO),
         20: ("BOOT_CFG", I), 22: ("UART2_TXD", O), 23: ("UART2_RXD", I), 24: ("USB_VBUS", PI),
         25: ("USB_DP", B), 26: ("USB_DM", B), 28: ("NC", NC), 29: ("NC", NC), 32: ("RF_ANT", P),
         34: ("VBAT", PI), 35: ("VBAT", PI), 38: ("ADC", I), 39: ("PWRKEY", I), 40: ("VDD_EXT", PO),
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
